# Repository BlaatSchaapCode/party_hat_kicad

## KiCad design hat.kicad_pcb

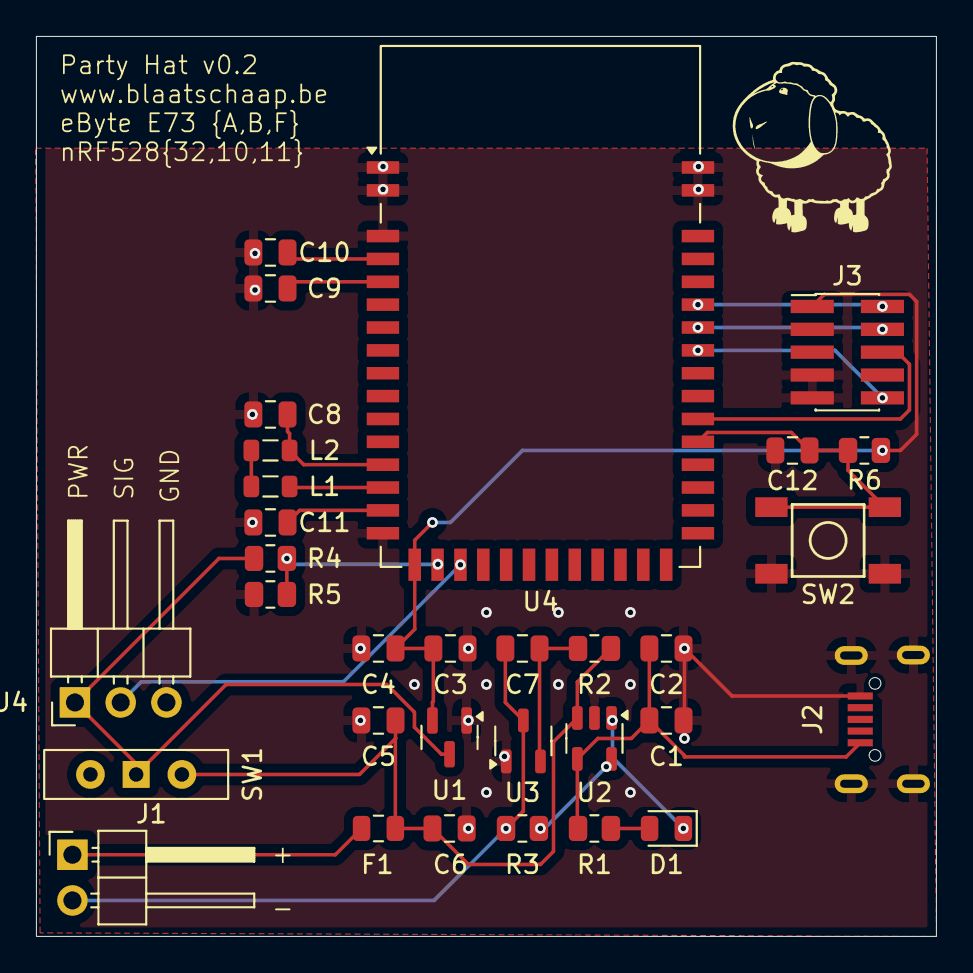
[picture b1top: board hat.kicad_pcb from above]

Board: 2 copper layers, 50.0 x 50.0 mm, 32 parts (0 on the bottom side), 24 nets.

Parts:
C1, C3, C5: 10u; C_0805_2012Metric
C2, C4, C6: 1u; C_0805_2012Metric
C7: 100n; C_0805_2012Metric
C8: 1 uF; C_0805_2012Metric
C9, C10: 100 pF; C_0805_2012Metric
C11, C12: 100 nF; C_0805_2012Metric
D1: LED; LED_0805_2012Metric
F1: Polyfuse_Small; Fuse_0805_2012Metric
J1: Conn_01x02; PinHeader_1x02_P2.54mm_Horizontal
J2: USB_B_Micro; USB_Micro-B_XKB_U254-05XX-4BH806
J3: Conn_02x05_Odd_Even; PinHeader_2x05_P1.27mm_Vertical_SMD
J4: Conn_01x03; PinHeader_1x03_P2.54mm_Horizontal
L1: 10 uH; L_0805_2012Metric
L2: 15 nH; L_0805_2012Metric
R1: 1K; R_0805_2012Metric
R2: 100R; R_0805_2012Metric
R3: 2K2; R_0805_2012Metric
R4, R5: 100 k; R_0805_2012Metric
R6: 10k; R_0805_2012Metric
SW1: SW_SPDT; SW_Slide-03_Wuerth-WS-SLTV_10x2.5x6.4_P2.54mm
SW2: SW_Push; TS-1187
U1: LDO 3V3; SOT-23
U2: LTC4054ES5-4.2; TSOT-23-5
U3: XB330xS; SOT-23-3
U4: E73-2G4M04S-52832; E73-2G4M04S

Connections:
+3V3: C3.2, C4.2, J3.1, R6.1, U1.2 (VO), U4.16 (VCC)
+BATT: C5.2, C6.2, F1.2, R2.1, SW1.2 (B), U2.3 (BAT)
-BATT: C7.1, J1.2, R3.2, U3.3 (GND)
BAT_MEAS: R4.2, R5.1, U4.17 (AIN0/P0.02)
BTN: C12.1, R6.2, SW2.1, U4.32 (P0.17)
DCC: L1.1, U4.13 (DCC)
DEC1: C11.1, U4.14 (DEC1)
DEC2: C10.1, U4.3 (DEC2)
DEC3: C9.1, U4.4 (DEC3)
DEC4: C8.1, L2.2, U4.12 (DEC4)
GND: C1.1, C2.1, C3.1, C4.1, C5.1, C6.1, C8.2, C9.2, C10.2, C11.2, C12.2, J2.5 (GND), J2.6 (Shield), J3.3, J3.7, J3.9, J4.3, R5.2, SW2.2, U1.1 (GND), U2.2 (GND), U3.1 (VM), U4.0 (GND), U4.1 (GND), U4.2 (GND), U4.15 (GND), U4.42 (GND), U4.43 (GND)
unnamed: D1.2 (A), R1.2
unnamed: D1.1 (K), U2.1 (~CHRG)
unnamed: F1.1, J1.1
unnamed: L1.2, L2.1
unnamed: R3.1, U2.5 (PROG)
unnamed: C7.2, R2.2, U3.2 (VDD)
PWR: J4.1, R4.1, SW1.1 (A), U1.3 (VI)
SIG: J4.2, U4.18 (AIN1/P0.03)
SWCLK: J3.4, U4.37 (SWDCLK)
SWDIO: J3.2, U4.38 (SWDIO)
SWO: J3.6, U4.33 (SWO/P0.18)
VBUS: C1.2, C2.2, J2.1 (VBUS), R1.1, U2.4 (V_{CC})
nSRST: J3.10, U4.36 (P0.21/~RESET)

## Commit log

2024-07-05 Party Hat v0.1
2024-07-05 Fix power on debug connector
2024-07-05 fix c12 footprint
2024-07-11 fix footprint
